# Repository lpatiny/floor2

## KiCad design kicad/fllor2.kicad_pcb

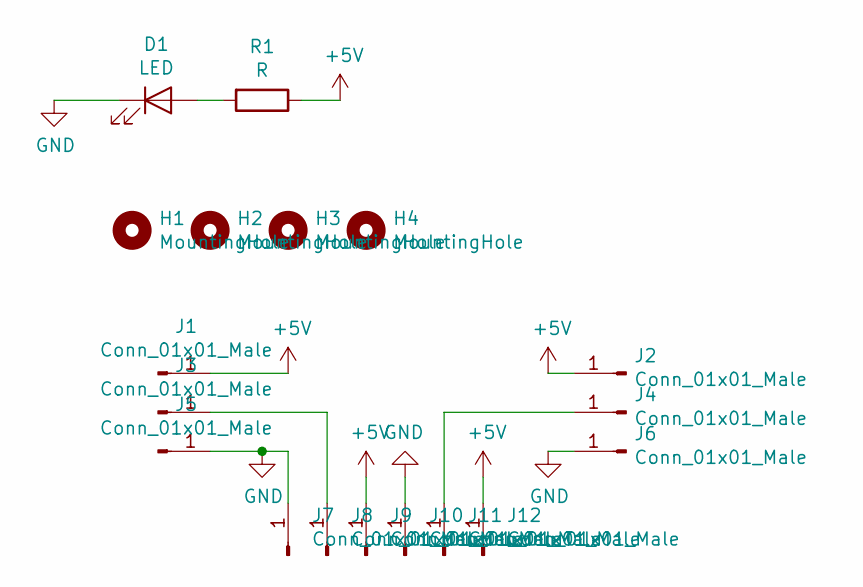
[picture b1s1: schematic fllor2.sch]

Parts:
D1: LED; LED_0805_2012Metric_Pad1.15x1.40mm_HandSolder
H1, H2, H3, H4: MountingHole; MountingHole_3.2mm_M3_Pad
J1, J2, J3, J4, J5, J6, J7, J8, J9, J10, J11, J12: Conn_01x01_Male; SolderWirePad_1x01_SMD_5x10mm
R1: R; R_0805_2012Metric_Pad1.15x1.40mm_HandSolder

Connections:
+5V: J1.1, J2.1, J9.1, J12.1, R1.1
GND: D1.1 (K), J5.1, J6.1, J7.1, J10.1
unnamed: D1.2 (A), R1.2
unnamed: J3.1, J8.1
unnamed: J4.1, J11.1

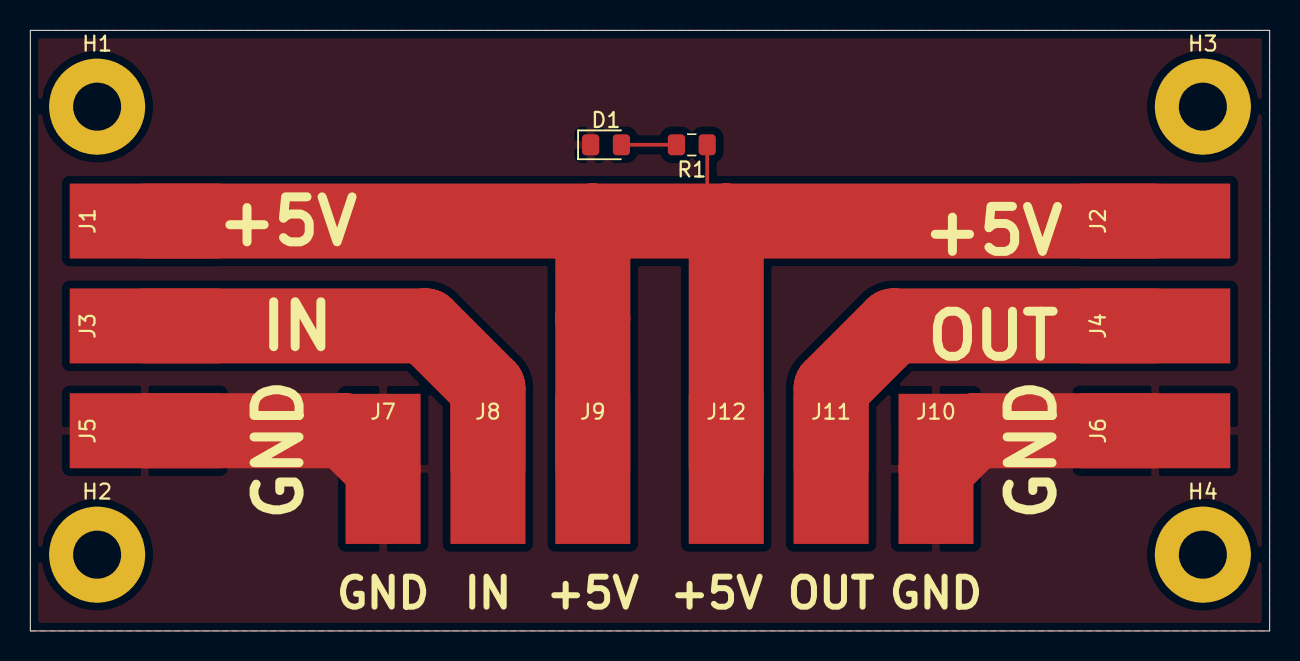
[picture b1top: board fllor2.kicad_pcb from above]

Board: 2 copper layers, 82.6 x 40.0 mm, 18 parts (0 on the bottom side), 5 nets.
